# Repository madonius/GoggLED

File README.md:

You will need the APA102 modules for KiCAD on https://github.com/tylercrumpton/CrumpPrints.pretty

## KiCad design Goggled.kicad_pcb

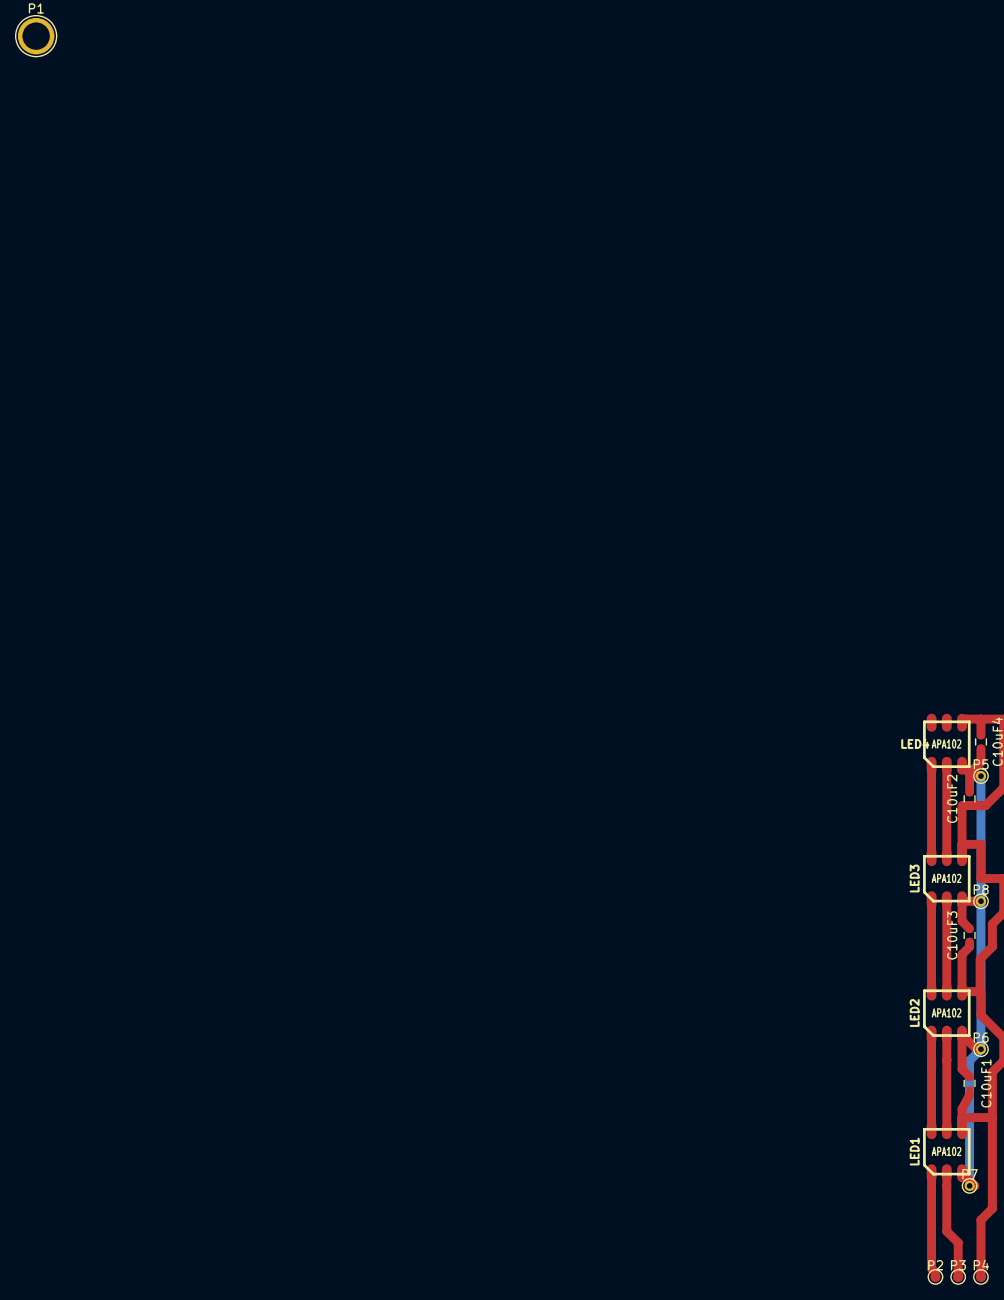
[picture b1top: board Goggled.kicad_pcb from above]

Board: 2 copper layers, 16 parts (0 on the bottom side), 10 nets.

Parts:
C10uF1, C10uF2, C10uF3, C10uF4: CSMALL; C_0603
LED1, LED2, LED3, LED4: APA102
P1: CONN_01X01; 1pin
P2, P3, P4, P5, P6, P7, P8: CONN_01X01; PINTST

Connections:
GND: C10uF1.1, C10uF2.2, C10uF3.2, C10uF4.2, LED1.3, LED2.3, LED3.3, LED4.3, P5.1, P6.1, P7.1, P8.1
unnamed: C10uF1.2, C10uF2.1, C10uF3.1, C10uF4.1, LED1.4, LED2.4, LED3.4, LED4.4, P4.1
unnamed: LED1.1, P2.1
unnamed: LED1.2, P3.1
unnamed: LED1.5, LED2.2
unnamed: LED1.6, LED2.1
unnamed: LED2.5, LED3.2
unnamed: LED2.6, LED3.1
unnamed: LED3.5, LED4.2
unnamed: LED3.6, LED4.1

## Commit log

2016-05-26 One Commit to rule them all
2016-07-28 Added adaptations brightness
